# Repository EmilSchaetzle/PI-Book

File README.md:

# PI-Book
This repository features the development of a new Raspberry Pi based mobile laptop. This new laptop is optimized by focusing on battery life instead of computing power. A solar panel is used as well to guarantee the energy supply in areas with no access to electricity. Additionally we implemented several interfaces that are not usually found in modern laptops but are very effective for measuring and development such as a RS 232 port, I2C, or a few raw GPIO pins. The product itself could become a cost-efficient solution for developing countries.

[Building instructions](BUILDING_INSTRUCTIONS.md)

[German paper](PAPER_german.pdf)

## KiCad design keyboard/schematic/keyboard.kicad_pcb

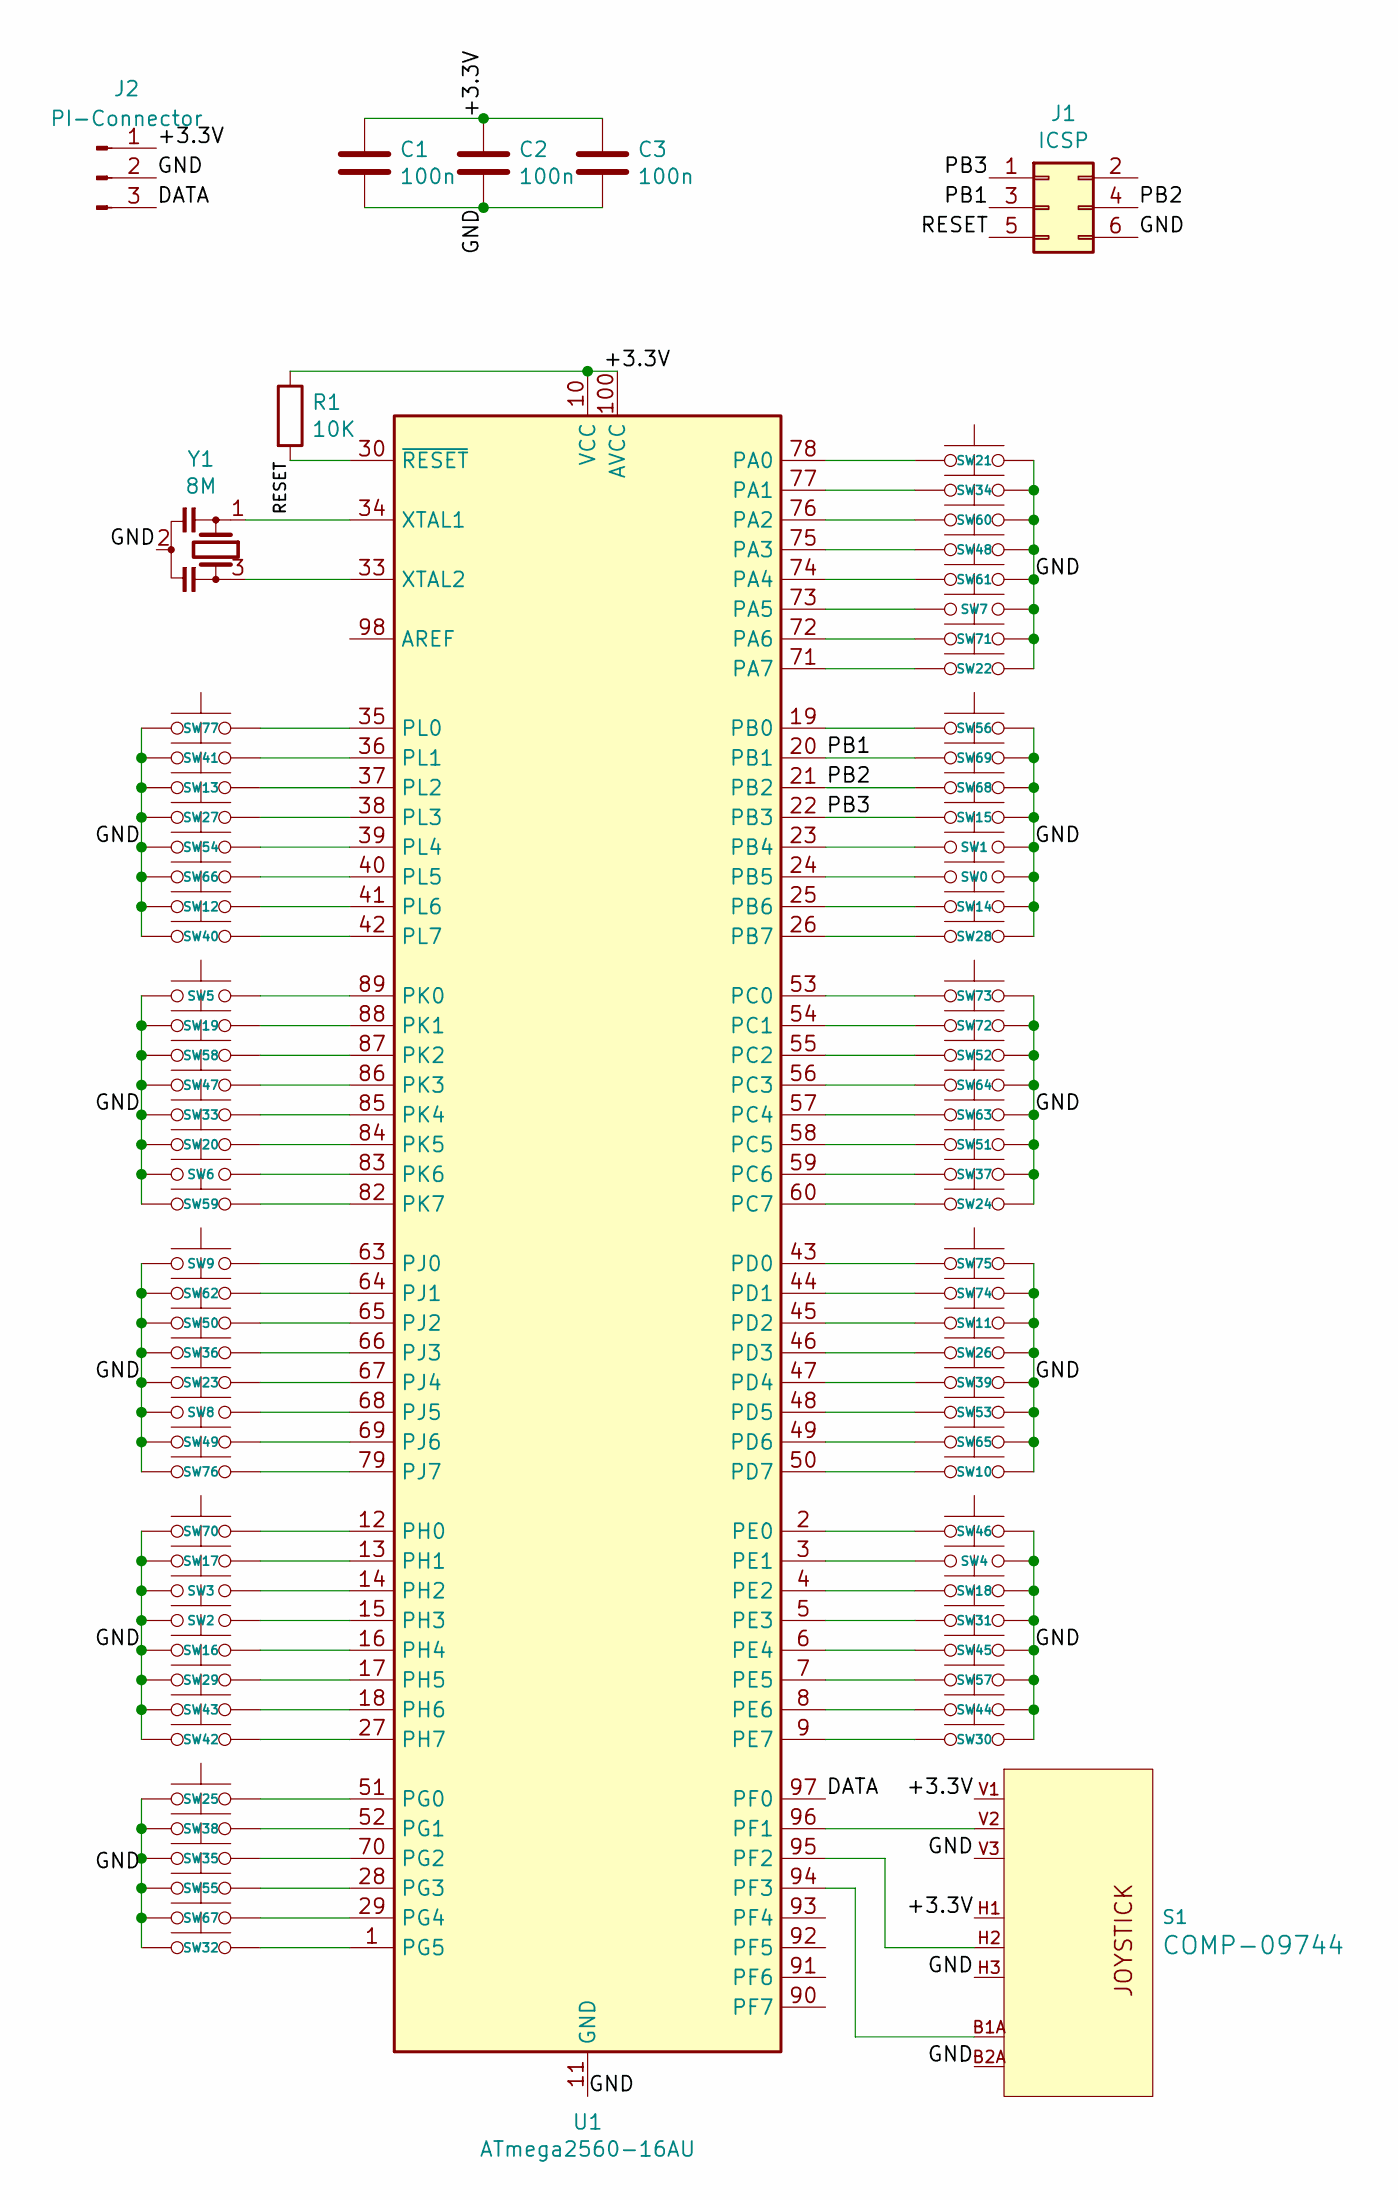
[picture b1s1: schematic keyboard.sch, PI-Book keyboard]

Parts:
C1, C2, C3: 100n; C_0201_0603Metric
J1: ICSP; PinHeader_2x03_P2.54mm_Vertical
J2: PI-Connector; PinHeader_1x03_P2.54mm_Vertical
R1: 10K; R_0201_0603Metric
S1: JOYSTICK_THUMB; JOYSTICK
SW0, SW1, SW2, SW3, SW4, SW5, SW6, SW7, SW8, SW9, SW10, SW11, SW12, SW13, SW14, SW15, SW16, SW17, SW18, SW19, SW20, SW21, SW22, SW23, SW24, SW25, SW26, SW27, SW28, SW29, SW30, SW31, SW32, SW33, SW34, SW35, SW36, SW37, SW38, SW39, SW40, SW41, SW42, SW43, SW44, SW45, SW46, SW47, SW48, SW49, SW50, SW51, SW52, SW53, SW54, SW55, SW56, SW57, SW58, SW59, SW60, SW61, SW62, SW63, SW64, SW65, SW66, SW67, SW68, SW69, SW70, SW71, SW72, SW73, SW74, SW75, SW76, SW77: SW_Push; SW_PUSH_6mm_H5mm
U1: ATmega2560-16AU; TQFP-100_14x14mm_P0.5mm
Y1: 8M; Resonator-3Pin_W6.0mm_H3.0mm

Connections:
/+3.3V: C1.1, C2.1, C3.1, J2.1, R1.1, S1.H1 (H+), S1.V1 (V+), U1.10 (VCC), U1.31 (VCC), U1.61 (VCC), U1.80 (VCC), U1.100 (AVCC)
/DATA: J2.3, U1.97 (PF0)
/GND: C1.2, C2.2, C3.2, J1.6, J2.2, S1.B2A (SEL-), S1.H3 (H-), S1.V3 (V-), SW0.1, SW1.1, SW2.1, SW3.1, SW4.1, SW5.1, SW6.1, SW7.1, SW8.1, SW9.1, SW10.1, SW11.1, SW12.1, SW13.1, SW14.1, SW15.1, SW16.1, SW17.1, SW18.1, SW19.1, SW20.1, SW21.1, SW22.1, SW23.1, SW24.1, SW25.1, SW26.1, SW27.1, SW28.1, SW29.1, SW30.1, SW31.1, SW32.1, SW33.1, SW34.1, SW35.1, SW36.1, SW37.1, SW38.1, SW39.1, SW40.1, SW41.1, SW42.1, SW43.1, SW44.1, SW45.1, SW46.1, SW47.1, SW48.1, SW49.1, SW50.1, SW51.1, SW52.1, SW53.1, SW54.1, SW55.1, SW56.1, SW57.1, SW58.1, SW59.1, SW60.1, SW61.1, SW62.1, SW63.1, SW64.1, SW65.1, SW66.1, SW67.1, SW68.1, SW69.1, SW70.1, SW71.2, SW72.1, SW73.1, SW74.1, SW75.1, SW76.2, SW77.1, U1.11 (GND), U1.32 (GND), U1.62 (GND), U1.81 (GND), U1.99 (GND), Y1.2
/PB1: J1.3, SW69.2, U1.20 (PB1)
/PB2: J1.4, SW68.2, U1.21 (PB2)
/PB3: J1.1, SW15.2, U1.22 (PB3)
/RESET: J1.5, R1.2, U1.30 (~RESET)
unnamed: S1.B1A (SEL+), U1.94 (PF3)
unnamed: S1.H2 (H), U1.95 (PF2)
unnamed: S1.V2 (V), U1.96 (PF1)
unnamed: SW0.2, U1.24 (PB5)
unnamed: SW1.2, U1.23 (PB4)
unnamed: SW2.2, U1.15 (PH3)
unnamed: SW3.2, U1.14 (PH2)
unnamed: SW4.2, U1.3 (PE1)
unnamed: SW5.2, U1.89 (PK0)
unnamed: SW6.2, U1.83 (PK6)
unnamed: SW7.2, U1.73 (PA5)
unnamed: SW8.2, U1.68 (PJ5)
unnamed: SW9.2, U1.63 (PJ0)
unnamed: SW10.2, U1.50 (PD7)
unnamed: SW11.2, U1.45 (PD2)
unnamed: SW12.2, U1.41 (PL6)
unnamed: SW13.2, U1.37 (PL2)
unnamed: SW14.2, U1.25 (PB6)
unnamed: SW16.2, U1.16 (PH4)
unnamed: SW17.2, U1.13 (PH1)
unnamed: SW18.2, U1.4 (PE2)
unnamed: SW19.2, U1.88 (PK1)
unnamed: SW20.2, U1.84 (PK5)
unnamed: SW21.2, U1.78 (PA0)
unnamed: SW22.2, U1.71 (PA7)
unnamed: SW23.2, U1.67 (PJ4)
unnamed: SW24.2, U1.60 (PC7)
unnamed: SW25.2, U1.51 (PG0)
unnamed: SW26.2, U1.46 (PD3)
unnamed: SW27.2, U1.38 (PL3)
unnamed: SW28.2, U1.26 (PB7)
unnamed: SW29.2, U1.17 (PH5)
unnamed: SW30.2, U1.9 (PE7)
unnamed: SW31.2, U1.5 (PE3)
unnamed: SW32.2, U1.1 (PG5)
unnamed: SW33.2, U1.85 (PK4)
unnamed: SW34.2, U1.77 (PA1)
unnamed: SW35.2, U1.70 (PG2)
unnamed: SW36.2, U1.66 (PJ3)
unnamed: SW37.2, U1.59 (PC6)
unnamed: SW38.2, U1.52 (PG1)
unnamed: SW39.2, U1.47 (PD4)
unnamed: SW40.2, U1.42 (PL7)
unnamed: SW41.2, U1.36 (PL1)
unnamed: SW42.2, U1.27 (PH7)
unnamed: SW43.2, U1.18 (PH6)
unnamed: SW44.2, U1.8 (PE6)
unnamed: SW45.2, U1.6 (PE4)
unnamed: SW46.2, U1.2 (PE0)
unnamed: SW47.2, U1.86 (PK3)
unnamed: SW48.2, U1.75 (PA3)
unnamed: SW49.2, U1.69 (PJ6)
unnamed: SW50.2, U1.65 (PJ2)
unnamed: SW51.2, U1.58 (PC5)
unnamed: SW52.2, U1.55 (PC2)
unnamed: SW53.2, U1.48 (PD5)
unnamed: SW54.2, U1.39 (PL4)
unnamed: SW55.2, U1.28 (PG3)
unnamed: SW56.2, U1.19 (PB0)
unnamed: SW57.2, U1.7 (PE5)
unnamed: SW58.2, U1.87 (PK2)
unnamed: SW59.2, U1.82 (PK7)
unnamed: SW60.2, U1.76 (PA2)
unnamed: SW61.2, U1.74 (PA4)
unnamed: SW62.2, U1.64 (PJ1)
unnamed: SW63.2, U1.57 (PC4)
unnamed: SW64.2, U1.56 (PC3)
unnamed: SW65.2, U1.49 (PD6)
unnamed: SW66.2, U1.40 (PL5)
unnamed: SW67.2, U1.29 (PG4)
unnamed: SW70.2, U1.12 (PH0)
unnamed: SW71.1, U1.72 (PA6)
unnamed: SW72.2, U1.54 (PC1)
unnamed: SW73.2, U1.53 (PC0)
unnamed: SW74.2, U1.44 (PD1)
unnamed: SW75.2, U1.43 (PD0)
unnamed: SW76.1, U1.79 (PJ7)
unnamed: SW77.2, U1.35 (PL0)
unnamed: U1.33 (XTAL2), Y1.3
unnamed: U1.34 (XTAL1), Y1.1

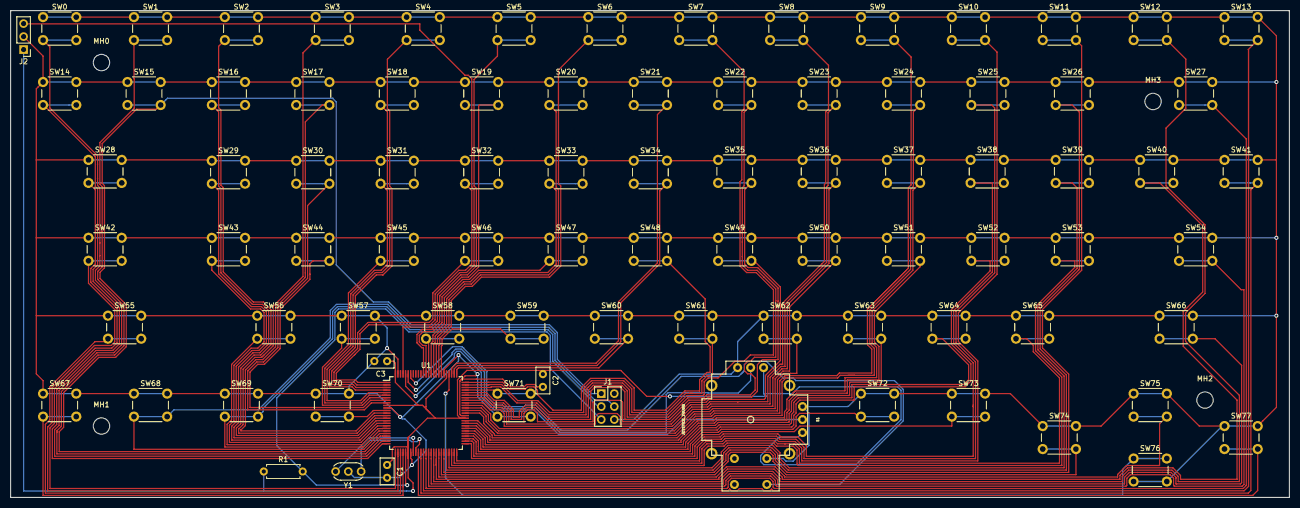
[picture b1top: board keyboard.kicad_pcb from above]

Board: 2 copper layers, 250.2 x 95.2 mm, 91 parts (0 on the bottom side), 87 nets.

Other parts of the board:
MH0, MH1, MH2, MH3: MountingHole_3.2mm_M3

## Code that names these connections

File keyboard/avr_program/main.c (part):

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
inline void high()
{
    PORTF |= (1 << PF0);
    del();
}

inline void low()
{
    PORTF &= ~(1 << PF0);
    del();
}
void send(uint8_t value)
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void send_initial_state()
{
    // Send key states
    send_key_state(21, PINA & (1 << PA0));
    send_key_state(34, PINA & (1 << PA1));
    send_key_state(60, PINA & (1 << PA2));
    send_key_state(48, PINA & (1 << PA3));
    send_key_state(61, PINA & (1 << PA4));
    send_key_state(7, PINA & (1 << PA5));
    send_key_state(71, PINA & (1 << PA6));
    send_key_state(22, PINA & (1 << PA7));

    send_key_state(56, PINB & (1 << PB0));
    send_key_state(69, PINB & (1 << PB1));
    send_key_state(68, PINB & (1 << PB2));
    send_key_state(15, PINB & (1 << PB3));
    send_key_state(1, PINB & (1 << PB4));
    send_key_state(0, PINB & (1 << PB5));
    send_key_state(14, PINB & (1 << PB6));
    send_key_state(28, PINB & (1 << PB7));

    send_key_state(73, PINC & (1 << PC0));
    send_key_state(72, PINC & (1 << PC1));
    send_key_state(52, PINC & (1 << PC2));
    send_key_state(64, PINC & (1 << PC3));
    send_key_state(63, PINC & (1 << PC4));
    send_key_state(51, PINC & (1 << PC5));
    send_key_state(37, PINC & (1 << PC6));
    send_key_state(24, PINC & (1 << PC7));

    send_key_state(75, PIND & (1 << PD0));
    send_key_state(74, PIND & (1 << PD1));
    send_key_state(11, PIND & (1 << PD2));
    send_key_state(26, PIND & (1 << PD3));
    send_key_state(39, PIND & (1 << PD4));
    send_key_state(53, PIND & (1 << PD5));
    send_key_state(65, PIND & (1 << PD6));
    send_key_state(10, PIND & (1 << PD7));

    send_key_state(46, PINE & (1 << PE0));
    send_key_state(4, PINE & (1 << PE1));
    send_key_state(18, PINE & (1 << PE2));
    send_key_state(31, PINE & (1 << PE3));
    send_key_state(45, PINE & (1 << PE4));
    send_key_state(57, PINE & (1 << PE5));
    send_key_state(44, PINE & (1 << PE6));
    send_key_state(30, PINE & (1 << PE7));

    send_key_state(70, PINH & (1 << PH0));
    send_key_state(17, PINH & (1 << PH1));
    send_key_state(3, PINH & (1 << PH2));
    send_key_state(2, PINH & (1 << PH3));
    send_key_state(16, PINH & (1 << PH4));
    send_key_state(29, PINH & (1 << PH5));
    send_key_state(43, PINH & (1 << PH6));
    send_key_state(42, PINH & (1 << PH7));

    send_key_state(9, PINJ & (1 << PJ0));
    send_key_state(62, PINJ & (1 << PJ1));
    send_key_state(50, PINJ & (1 << PJ2));
    send_key_state(36, PINJ & (1 << PJ3));
    send_key_state(23, PINJ & (1 << PJ4));
    send_key_state(8, PINJ & (1 << PJ5));
    send_key_state(49, PINJ & (1 << PJ6));
    send_key_state(76, PINJ & (1 << PJ7));

    send_key_state(77, PINL & (1 << PL0));
    send_key_state(41, PINL & (1 << PL1));
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    send_key_state(12, PINL & (1 << PL6));
    send_key_state(40, PINL & (1 << PL7));

    send_key_state(5, PINK & (1 << PK0));
    send_key_state(19, PINK & (1 << PK1));
    send_key_state(58, PINK & (1 << PK2));
    send_key_state(47, PINK & (1 << PK3));
    send_key_state(33, PINK & (1 << PK4));
    send_key_state(20, PINK & (1 << PK5));
    send_key_state(6, PINK & (1 << PK6));
    send_key_state(59, PINK & (1 << PK7));

    send_key_state(25, PING & (1 << PG0));
    send_key_state(38, PING & (1 << PG1));
    send_key_state(35, PING & (1 << PG2));
    send_key_state(55, PING & (1 << PG3));
    send_key_state(67, PING & (1 << PG4));
    send_key_state(32, PING & (1 << PG5));

    // Send button state:
    send_button_state((PINF & (1 << PF3)));
}

void refresh_state()
{
    if (PINA != LPINA)
    {
        if ((PINA & (1 << PA0)) != (LPINA & (1 << PA0)))
        {
            send_key_state(21, (PINA & (1 << PA0)));
            LPINA ^= 1 << PA0;
        }
        if ((PINA & (1 << PA1)) != (LPINA & (1 << PA1)))
        {
            send_key_state(34, (PINA & (1 << PA1)));
            LPINA ^= 1 << PA1;
        }
        if ((PINA & (1 << PA2)) != (LPINA & (1 << PA2)))
        {
            send_key_state(60, (PINA & (1 << PA2)));
            LPINA ^= 1 << PA2;
        }
        if ((PINA & (1 << PA3)) != (LPINA & (1 << PA3)))
        {
            send_key_state(48, (PINA & (1 << PA3)));
            LPINA ^= 1 << PA3;
        }
        if ((PINA & (1 << PA4)) != (LPINA & (1 << PA4)))
        {
            send_key_state(61, (PINA & (1 << PA4)));
            LPINA ^= 1 << PA4;
        }
        if ((PINA & (1 << PA5)) != (LPINA & (1 << PA5)))
        {
            send_key_state(7, (PINA & (1 << PA5)));
            LPINA ^= 1 << PA5;
        }
        if ((PINA & (1 << PA6)) != (LPINA & (1 << PA6)))
        {
            send_key_state(71, (PINA & (1 << PA6)));
            LPINA ^= 1 << PA6;
        }
        if ((PINA & (1 << PA7)) != (LPINA & (1 << PA7)))
        {
            send_key_state(22, (PINA & (1 << PA7)));
            LPINA ^= 1 << PA7;
        }
    }

    if (PINB != LPINB)
    {
        if ((PINB & (1 << PB0)) != (LPINB & (1 << PB0)))
        {
            send_key_state(56, (PINB & (1 << PB0)));
            LPINB ^= 1 << PB0;
        }
        if ((PINB & (1 << PB1)) != (LPINB & (1 << PB1)))
        {
            send_key_state(69, (PINB & (1 << PB1)));
            LPINB ^= 1 << PB1;
        }
        if ((PINB & (1 << PB2)) != (LPINB & (1 << PB2)))
        {
            send_key_state(68, (PINB & (1 << PB2)));
            LPINB ^= 1 << PB2;
        }
        if ((PINB & (1 << PB3)) != (LPINB & (1 << PB3)))
        {
            send_key_state(15, (PINB & (1 << PB3)));
            LPINB ^= 1 << PB3;
        }
        if ((PINB & (1 << PB4)) != (LPINB & (1 << PB4)))
        {
            send_key_state(1, (PINB & (1 << PB4)));
            LPINB ^= 1 << PB4;
        }
        if ((PINB & (1 << PB5)) != (LPINB & (1 << PB5)))
        {
            send_key_state(0, (PINB & (1 << PB5)));
            LPINB ^= 1 << PB5;
        }
        if ((PINB & (1 << PB6)) != (LPINB & (1 << PB6)))
        {
            send_key_state(14, (PINB & (1 << PB6)));
            LPINB ^= 1 << PB6;
        }
        if ((PINB & (1 << PB7)) != (LPINB & (1 << PB7)))
        {
            send_key_state(28, (PINB & (1 << PB7)));
            LPINB ^= 1 << PB7;
        }
    }

    if (PINC != LPINC)
    {
        if ((PINC & (1 << PC0)) != (LPINC & (1 << PC0)))
        {
            send_key_state(73, (PINC & (1 << PC0)));
            LPINC ^= 1 << PC0;
        }
        if ((PINC & (1 << PC1)) != (LPINC & (1 << PC1)))
        {
            send_key_state(72, (PINC & (1 << PC1)));
            LPINC ^= 1 << PC1;
        }
        if ((PINC & (1 << PC2)) != (LPINC & (1 << PC2)))
        {
            send_key_state(52, (PINC & (1 << PC2)));
            LPINC ^= 1 << PC2;
        }
        if ((PINC & (1 << PC3)) != (LPINC & (1 << PC3)))
        {
            send_key_state(64, (PINC & (1 << PC3)));
            LPINC ^= 1 << PC3;
        }
        if ((PINC & (1 << PC4)) != (LPINC & (1 << PC4)))
        {
            send_key_state(63, (PINC & (1 << PC4)));
            LPINC ^= 1 << PC4;
        }
        if ((PINC & (1 << PC5)) != (LPINC & (1 << PC5)))
        {
            send_key_state(51, (PINC & (1 << PC5)));
            LPINC ^= 1 << PC5;
        }
        if ((PINC & (1 << PC6)) != (LPINC & (1 << PC6)))
        {
            send_key_state(37, (PINC & (1 << PC6)));
            LPINC ^= 1 << PC6;
        }
        if ((PINC & (1 << PC7)) != (LPINC & (1 << PC7)))
        {
            send_key_state(24, (PINC & (1 << PC7)));
            LPINC ^= 1 << PC7;
        }
    }

    if (PIND != LPIND)
    {
        if ((PIND & (1 << PD0)) != (LPIND & (1 << PD0)))
        {
            send_key_state(75, (PIND & (1 << PD0)));
            LPIND ^= 1 << PD0;
        }
        if ((PIND & (1 << PD1)) != (LPIND & (1 << PD1)))
        {
            send_key_state(74, (PIND & (1 << PD1)));
            LPIND ^= 1 << PD1;
        }
        if ((PIND & (1 << PD2)) != (LPIND & (1 << PD2)))
        {
            send_key_state(11, (PIND & (1 << PD2)));
            LPIND ^= 1 << PD2;
        }
        if ((PIND & (1 << PD3)) != (LPIND & (1 << PD3)))
        {
            send_key_state(26, (PIND & (1 << PD3)));
            LPIND ^= 1 << PD3;
        }
        if ((PIND & (1 << PD4)) != (LPIND & (1 << PD4)))
        {
            send_key_state(39, (PIND & (1 << PD4)));
            LPIND ^= 1 << PD4;
        }
        if ((PIND & (1 << PD5)) != (LPIND & (1 << PD5)))
        {
            send_key_state(53, (PIND & (1 << PD5)));
            LPIND ^= 1 << PD5;
        }
        if ((PIND & (1 << PD6)) != (LPIND & (1 << PD6)))
        {
            send_key_state(65, (PIND & (1 << PD6)));
            LPIND ^= 1 << PD6;
        }
        if ((PIND & (1 << PD7)) != (LPIND & (1 << PD7)))
        {
            send_key_state(10, (PIND & (1 << PD7)));
            LPIND ^= 1 << PD7;
        }
    }

    if (PINE != LPINE)
    {
        if ((PINE & (1 << PE0)) != (LPINE & (1 << PE0)))
        {
            send_key_state(46, (PINE & (1 << PE0)));
            LPINE ^= 1 << PE0;
        }
        if ((PINE & (1 << PE1)) != (LPINE & (1 << PE1)))
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
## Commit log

2018-08-05 First version of the keyboard programm as proof of concept. This programm will type am "a" using a virtual keyboard
2018-08-05 Changed bustype to serial
2018-08-06 Created extra functions for keyboard creation and keyDown/upEvents. Also added small test utility in main.c
2018-08-06 Update issue templates
2018-08-13 Splitted existing code in header and c file and improved formatinng. keyboard functions now begin with keyboard prefix
2018-08-15 First Version with about 0.9% Failure rate
2018-08-17 Removed old user space approach and inserted new kernel space solution. This solution is expermental and can cause kernel crashes but supports up to 500 bytes/s currently.
2018-08-18 Improved Timing. Transmission now super safe up to 10000 baud
2018-12-18 Converted Arduino to C. Still produces Kernel crashes.
2018-12-20 Fixed a bug, leading to kernel crashes. Not 100% save right now, but better. Working in Testenvironment.
2018-12-22 Added error handling during module loads. Formatted Code.
2018-12-24 Added support for the mouse button. Improved error handling. Fixed a Bug, causing a crash on reloading the module.
2018-12-26 Added joystick. Set Baud to 2000
2019-01-01 Changed mouse_factor to a module parameter; Renamed Kernel module. Changed AtMega clock to 500.000 kHz, optimized chip for energy saving.
2019-01-02 Added support for dkms
2019-01-02 Fixed a bug related to "_" with dkms
2019-01-03 Changed freq. to 125 Khz, fixed a bug, leading to timing problems at midnight.
2019-01-03 Changed F_CPU
2019-01-05 Added space
2019-01-22 Changed pin->key mapping
2019-01-22 Added GPIO schematics
2019-01-22 Added keyboard schematics
2019-01-22 Readded Protocol.txt
2019-01-23 Added schematic for power supply
2019-01-25 Generalized postbuild steps.
2019-02-01 Added dependencys
2019-02-02 Changed Oscillator to 8 MHz, set fuses to correct values
2019-02-02 Added waiting for raspberry pi kernel module to init
2019-02-04 Updated commands
2019-02-04 Fixed axes.
2019-02-07 Changed Format
2019-02-07 removed startup delay. Fixed bug, causing missinterpretation because of unintended interupt trigger
2019-02-07 Added power supply via pin Changed Timing to "ktime" Fixed bug, causing missinterpreation in first bytes. Added support for large time differences.
2019-02-07 Changed implementation of pin mapping
2019-02-10 Changed mapping of ADC value
2019-02-14 Added 3d files.
2019-03-26 Added Building Instructions
2019-03-26 Added german paper
2019-03-26 Added picture
